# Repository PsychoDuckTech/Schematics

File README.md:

# Schematic and PCB Files for PsychoDuck Tech PCBs

## Notes
35? GPIO pins on the ESP32-S3

22 pins for the keyboard - 6 rows, 16 cols

with the multiplexer - 11 pins - 6 rows, 5 cols

## Tutorial Brovsky
`git add -A`

`git commit -m "message here"`

`git push`

[Extensive Tutorial...](https://github.com/PsychoDuckTech/Schematics/blob/main/GitExtensiveTutorial.md)

## Useful Resources
[KiCanvas](https://kicanvas.org/)

[Discord Server](https://discord.gg/zeTJYsWzsf)

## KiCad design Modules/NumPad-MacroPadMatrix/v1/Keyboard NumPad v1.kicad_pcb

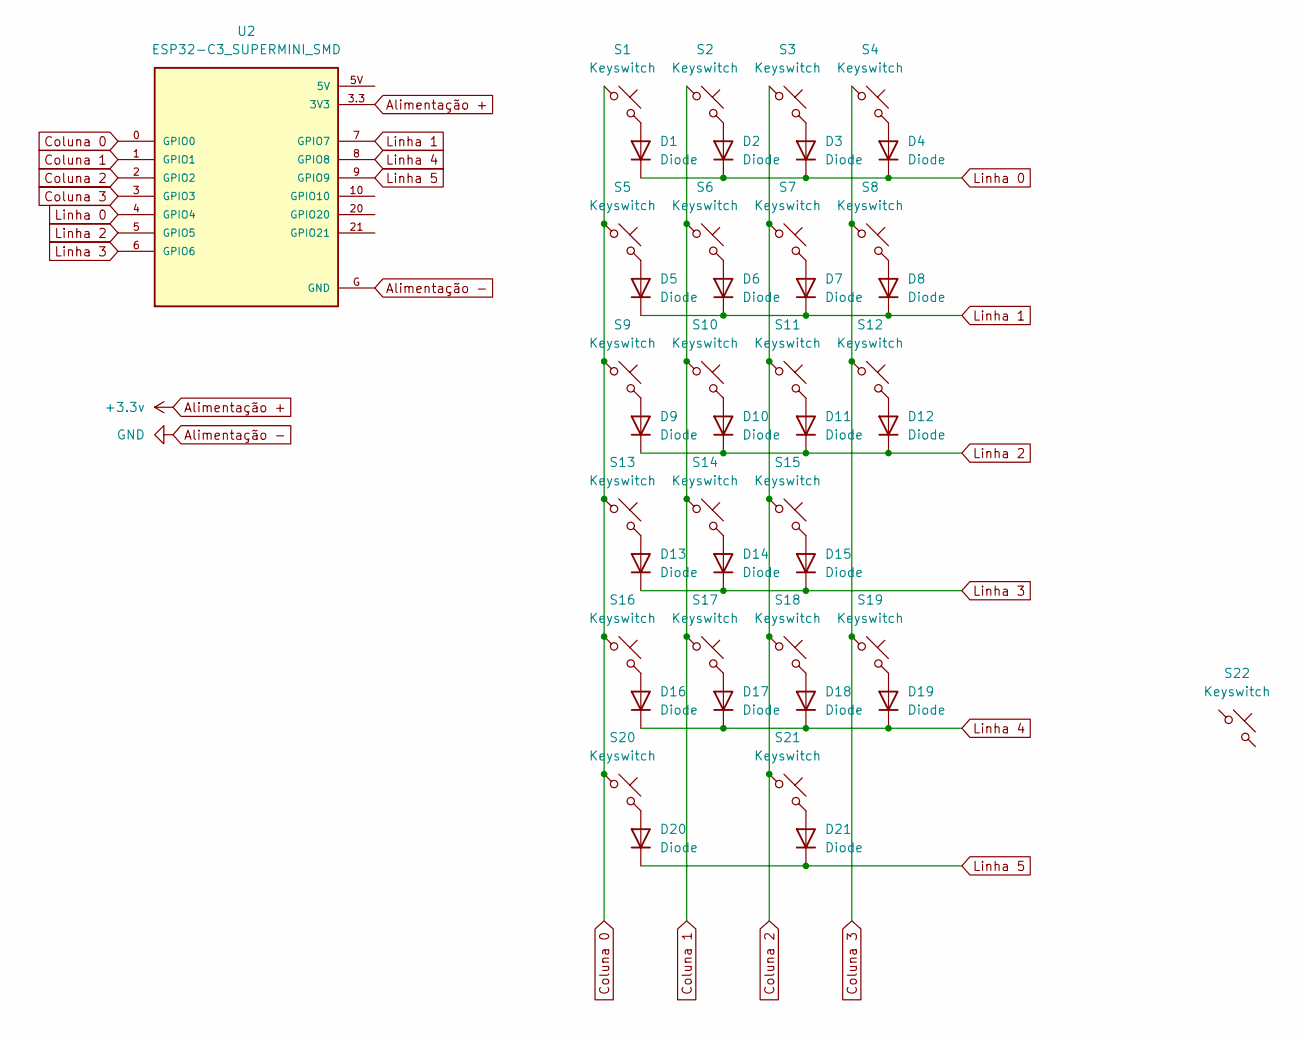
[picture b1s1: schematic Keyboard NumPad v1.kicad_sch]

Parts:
D1, D2, D3, D4, D5, D6, D7, D8, D9, D10, D11, D12, D13, D14, D15, D16, D17, D18, D19, D20, D21: Diode; D_DO-35_SOD27_P7.62mm_Horizontal
S1, S2, S3, S4, S5, S6, S7, S8, S9, S10, S11, S12, S13, S14, S15, S16, S17, S18, S19, S20, S21: Keyswitch; Hotswap_MX_Plated_1.00u
S22: Keyswitch; Cherry-MX-Low-Profile
U2: ESP32-C3_SUPERMINI_SMD; ESP32-C3_SUPERMINI

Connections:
Alimentação +: U2.3.3 (3V3)
Alimentação -: U2.G (GND)
Coluna 0: S1.1, S5.1, S9.1, S13.1, S16.1, S20.1, U2.0 (GPIO0)
Coluna 1: S2.1, S6.1, S10.1, S14.1, S17.1, U2.1 (GPIO1)
Coluna 2: S3.1, S7.1, S11.1, S15.1, S18.1, S21.1, U2.2 (GPIO2)
Coluna 3: S4.1, S8.1, S12.1, S19.1, U2.3 (GPIO3)
Linha 0: D1.1 (K), D2.1 (K), D3.1 (K), D4.1 (K), U2.4 (GPIO4)
Linha 1: D5.1 (K), D6.1 (K), D7.1 (K), D8.1 (K), U2.7 (GPIO7)
Linha 2: D9.1 (K), D10.1 (K), D11.1 (K), D12.1 (K), U2.5 (GPIO5)
Linha 3: D13.1 (K), D14.1 (K), D15.1 (K), U2.6 (GPIO6)
Linha 4: D16.1 (K), D17.1 (K), D18.1 (K), D19.1 (K), U2.8 (GPIO8)
Linha 5: D20.1 (K), D21.1 (K), U2.9 (GPIO9)
unnamed: D1.2 (A), S1.2
unnamed: D2.2 (A), S2.2
unnamed: D3.2 (A), S3.2
unnamed: D4.2 (A), S4.2
unnamed: D5.2 (A), S5.2
unnamed: D6.2 (A), S6.2
unnamed: D7.2 (A), S7.2
unnamed: D8.2 (A), S8.2
unnamed: D9.2 (A), S9.2
unnamed: D10.2 (A), S10.2
unnamed: D11.2 (A), S11.2
unnamed: D12.2 (A), S12.2
unnamed: D13.2 (A), S13.2
unnamed: D14.2 (A), S14.2
unnamed: D15.2 (A), S15.2
unnamed: D16.2 (A), S16.2
unnamed: D17.2 (A), S17.2
unnamed: D18.2 (A), S18.2
unnamed: D19.2 (A), S19.2
unnamed: D20.2 (A), S20.2
unnamed: D21.2 (A), S21.2

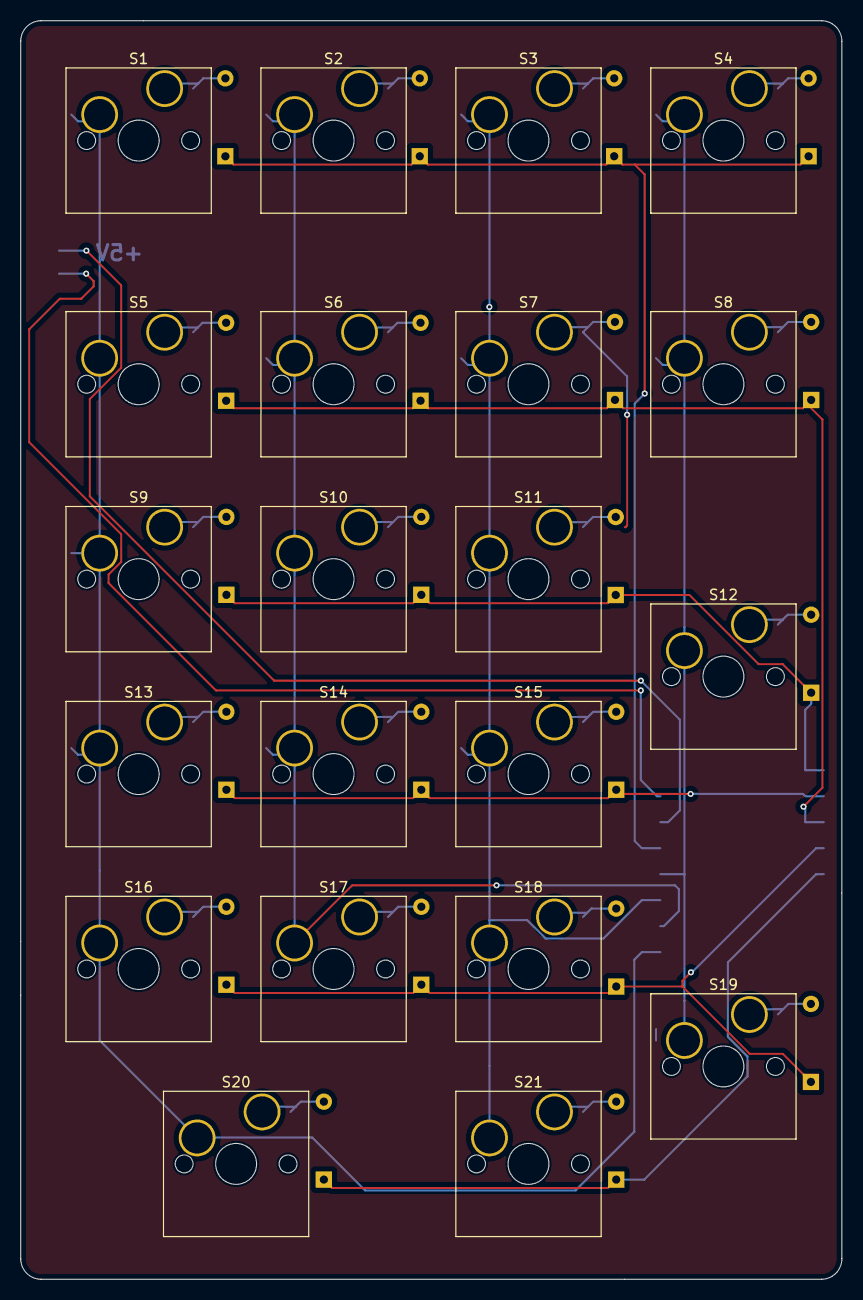
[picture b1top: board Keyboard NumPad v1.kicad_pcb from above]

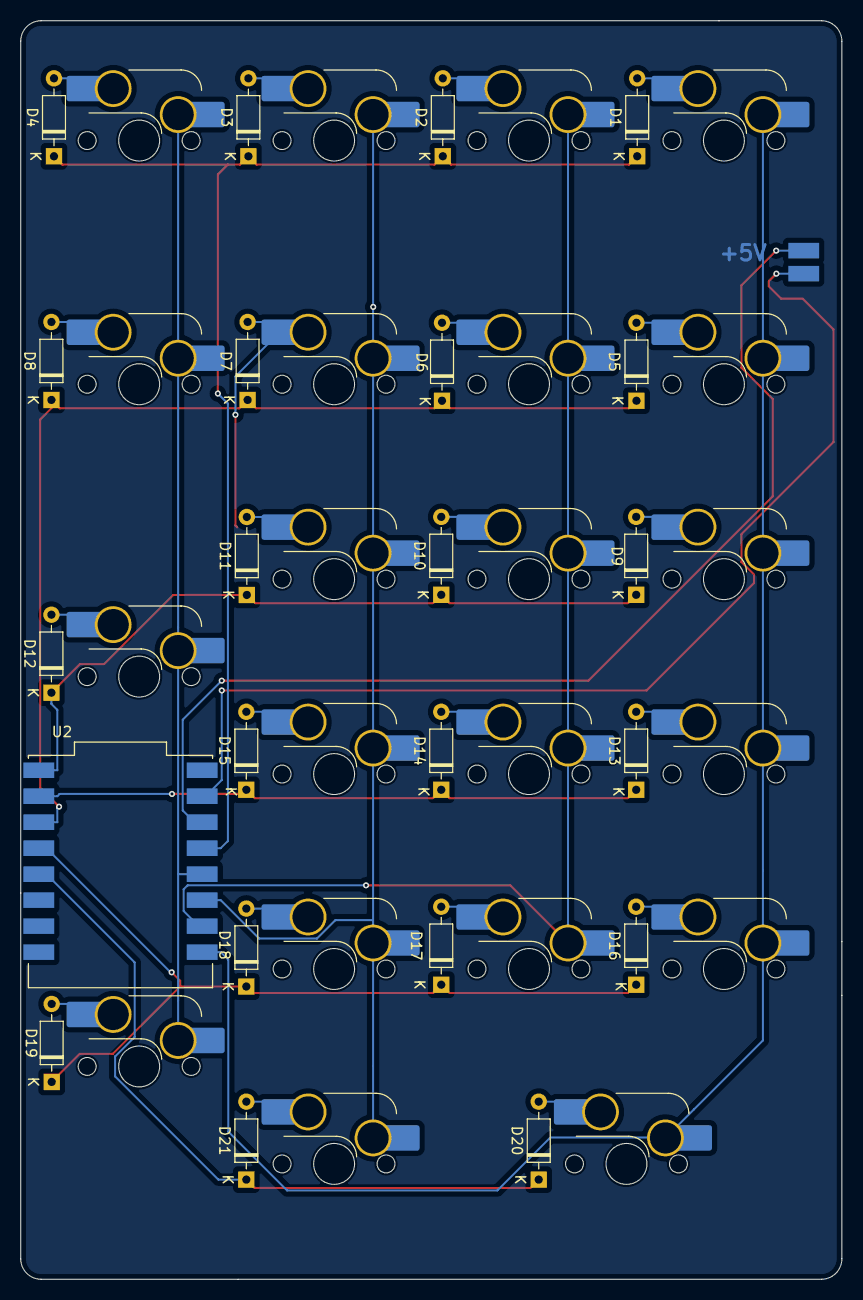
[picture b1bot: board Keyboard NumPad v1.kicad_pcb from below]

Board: 2 copper layers, 80.2 x 123.0 mm, 43 parts (22 on the bottom side), 31 nets.

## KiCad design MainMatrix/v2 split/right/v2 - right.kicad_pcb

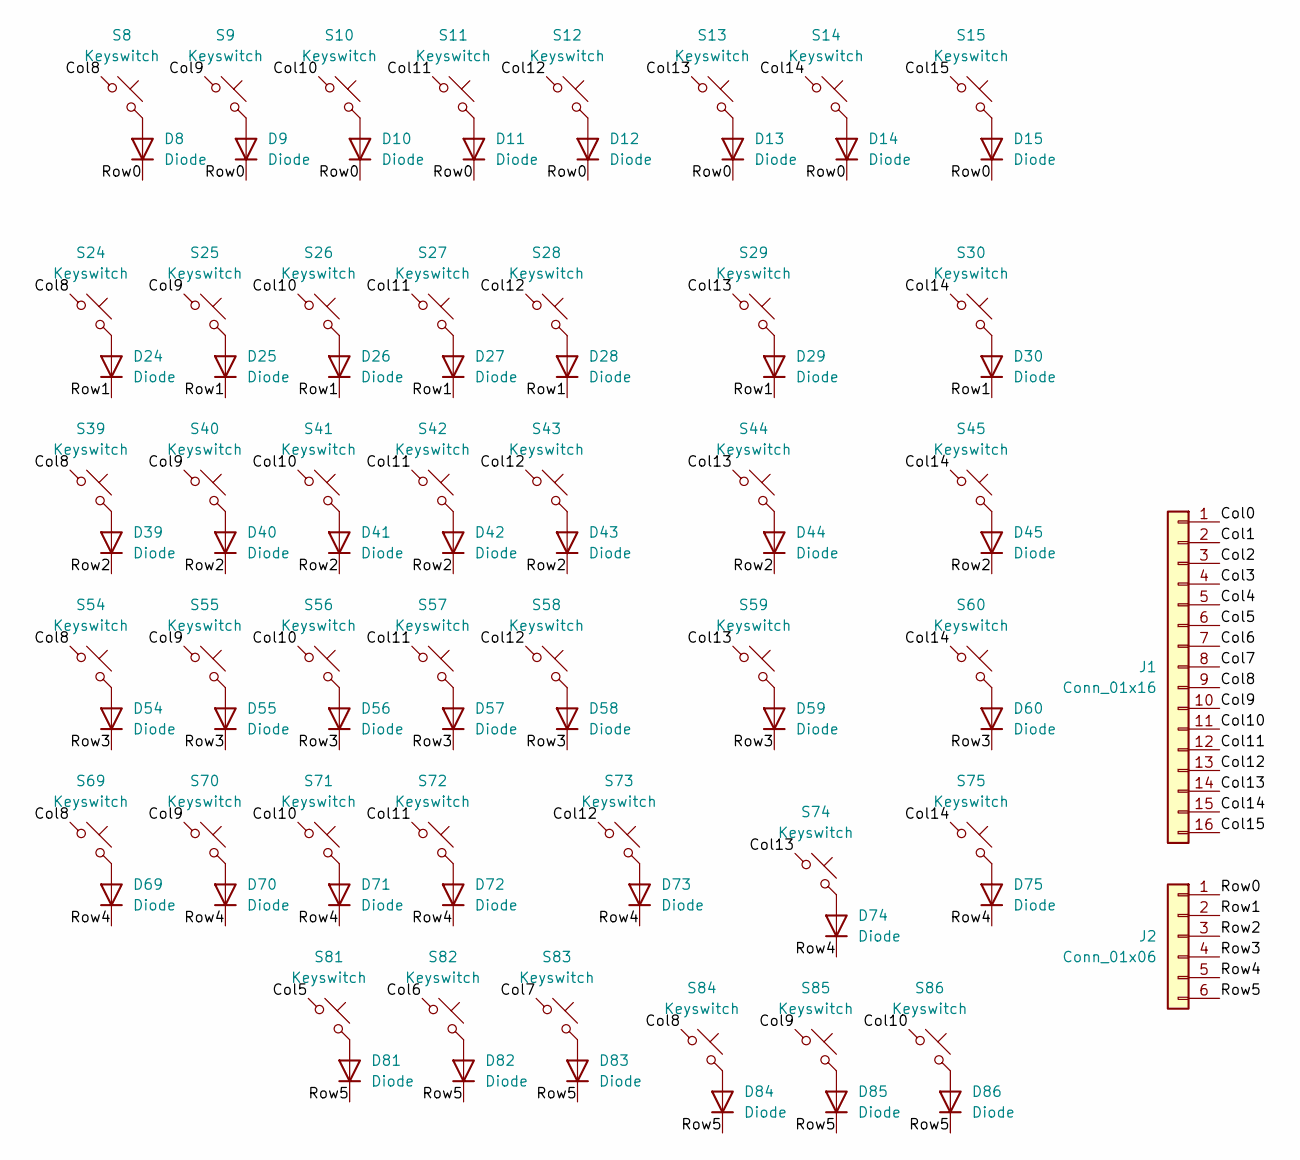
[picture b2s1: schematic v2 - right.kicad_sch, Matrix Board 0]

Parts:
D8, D9, D10, D11, D12, D13, D14, D15, D24, D25, D26, D27, D28, D29, D30, D39, D40, D41, D42, D43, D44, D45, D54, D55, D56, D57, D58, D59, D60, D69, D70, D71, D72, D73, D74, D75, D81, D82, D83, D84, D85, D86: Diode; D_DO-35_SOD27_P10.16mm_Horizontal
J1: Conn_01x16; PinSocket_1x16_P2.54mm_Vertical
J2: Conn_01x06; PinHeader_1x06_P2.54mm_Vertical
S8, S9, S10, S11, S12, S13, S14, S15, S24, S25, S26, S27, S28, S29, S30, S39, S40, S41, S42, S43, S44, S45, S54, S55, S56, S57, S58, S59, S60, S69, S70, S71, S72, S73, S74, S75, S81, S82, S83, S84, S85, S86: Keyswitch; Hotswap_MX_1.00u

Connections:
/Col0: J1.1
/Col1: J1.2
/Col2: J1.3
/Col3: J1.4
/Col4: J1.5
/Col5: J1.6, S81.1
/Col6: J1.7, S82.1
/Col7: J1.8, S83.1
/Col8: J1.9, S8.1, S24.1, S39.1, S54.1, S69.1, S84.1
/Col9: J1.10, S9.1, S25.1, S40.1, S55.1, S70.1, S85.1
/Col10: J1.11, S10.1, S26.1, S41.1, S56.1, S71.1, S86.1
/Col11: J1.12, S11.1, S27.1, S42.1, S57.1, S72.1
/Col12: J1.13, S12.1, S28.1, S43.1, S58.1, S73.1
/Col13: J1.14, S13.1, S29.1, S44.1, S59.1, S74.1
/Col14: J1.15, S14.1, S30.1, S45.1, S60.1, S75.1
/Col15: J1.16, S15.1
/Row0: D8.1 (K), D9.1 (K), D10.1 (K), D11.1 (K), D12.1 (K), D13.1 (K), D14.1 (K), D15.1 (K), J2.1
/Row1: D24.1 (K), D25.1 (K), D26.1 (K), D27.1 (K), D28.1 (K), D29.1 (K), D30.1 (K), J2.2
/Row2: D39.1 (K), D40.1 (K), D41.1 (K), D42.1 (K), D43.1 (K), D44.1 (K), D45.1 (K), J2.3
/Row3: D54.1 (K), D55.1 (K), D56.1 (K), D57.1 (K), D58.1 (K), D59.1 (K), D60.1 (K), J2.4
/Row4: D69.1 (K), D70.1 (K), D71.1 (K), D72.1 (K), D73.1 (K), D74.1 (K), D75.1 (K), J2.5
/Row5: D81.1 (K), D82.1 (K), D83.1 (K), D84.1 (K), D85.1 (K), D86.1 (K), J2.6
unnamed: D8.2 (A), S8.2
unnamed: D9.2 (A), S9.2
unnamed: D10.2 (A), S10.2
unnamed: D11.2 (A), S11.2
unnamed: D12.2 (A), S12.2
unnamed: D13.2 (A), S13.2
unnamed: D14.2 (A), S14.2
unnamed: D15.2 (A), S15.2
unnamed: D24.2 (A), S24.2
unnamed: D25.2 (A), S25.2
unnamed: D26.2 (A), S26.2
unnamed: D27.2 (A), S27.2
unnamed: D28.2 (A), S28.2
unnamed: D29.2 (A), S29.2
unnamed: D30.2 (A), S30.2
unnamed: D39.2 (A), S39.2
unnamed: D40.2 (A), S40.2
unnamed: D41.2 (A), S41.2
unnamed: D42.2 (A), S42.2
unnamed: D43.2 (A), S43.2
unnamed: D44.2 (A), S44.2
unnamed: D45.2 (A), S45.2
unnamed: D54.2 (A), S54.2
unnamed: D55.2 (A), S55.2
unnamed: D56.2 (A), S56.2
unnamed: D57.2 (A), S57.2
unnamed: D58.2 (A), S58.2
unnamed: D59.2 (A), S59.2
unnamed: D60.2 (A), S60.2
unnamed: D69.2 (A), S69.2
unnamed: D70.2 (A), S70.2
unnamed: D71.2 (A), S71.2
unnamed: D72.2 (A), S72.2
unnamed: D73.2 (A), S73.2
unnamed: D74.2 (A), S74.2
unnamed: D75.2 (A), S75.2
unnamed: D81.2 (A), S81.2
unnamed: D82.2 (A), S82.2
unnamed: D83.2 (A), S83.2
unnamed: D84.2 (A), S84.2
unnamed: D85.2 (A), S85.2
unnamed: D86.2 (A), S86.2

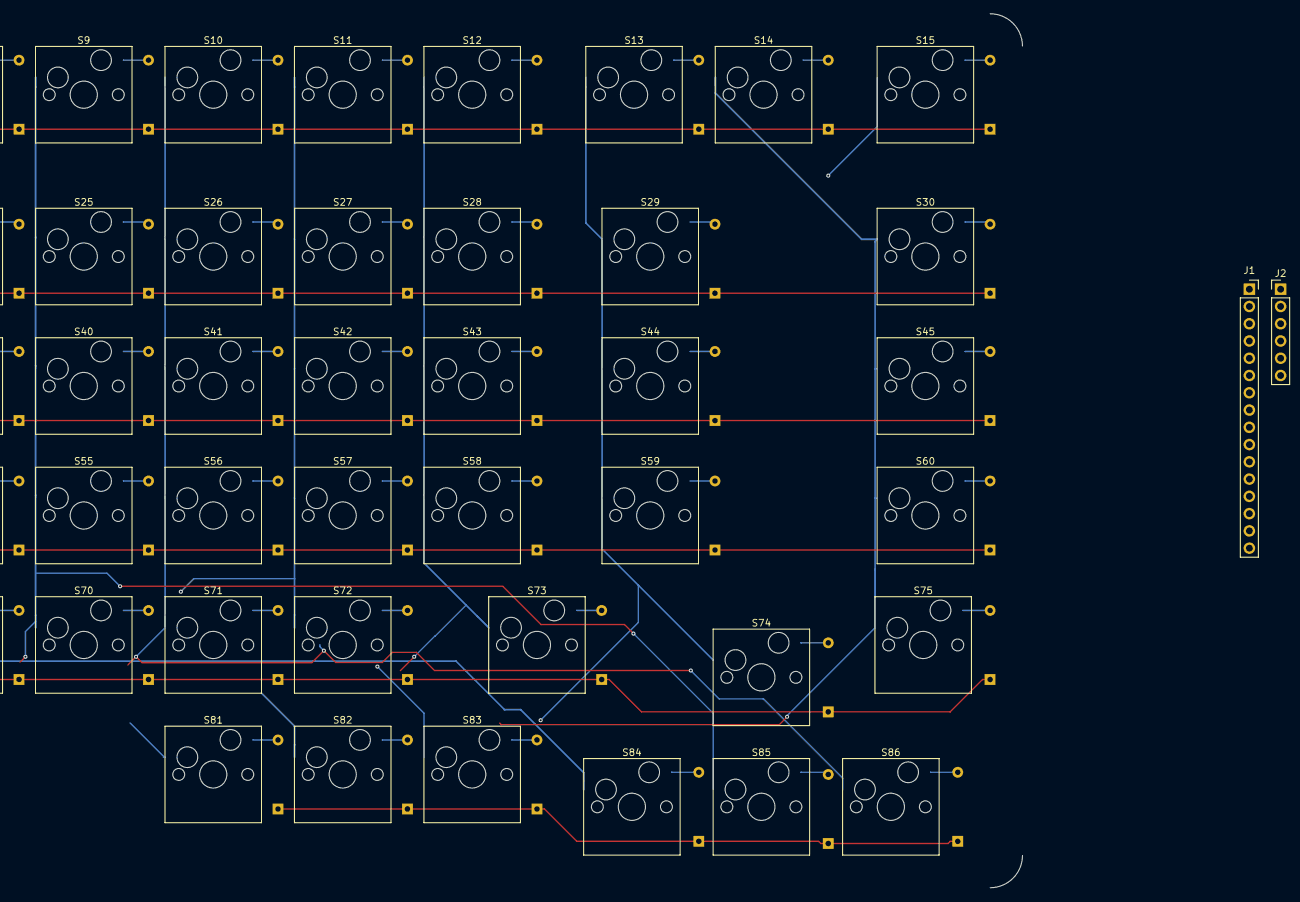
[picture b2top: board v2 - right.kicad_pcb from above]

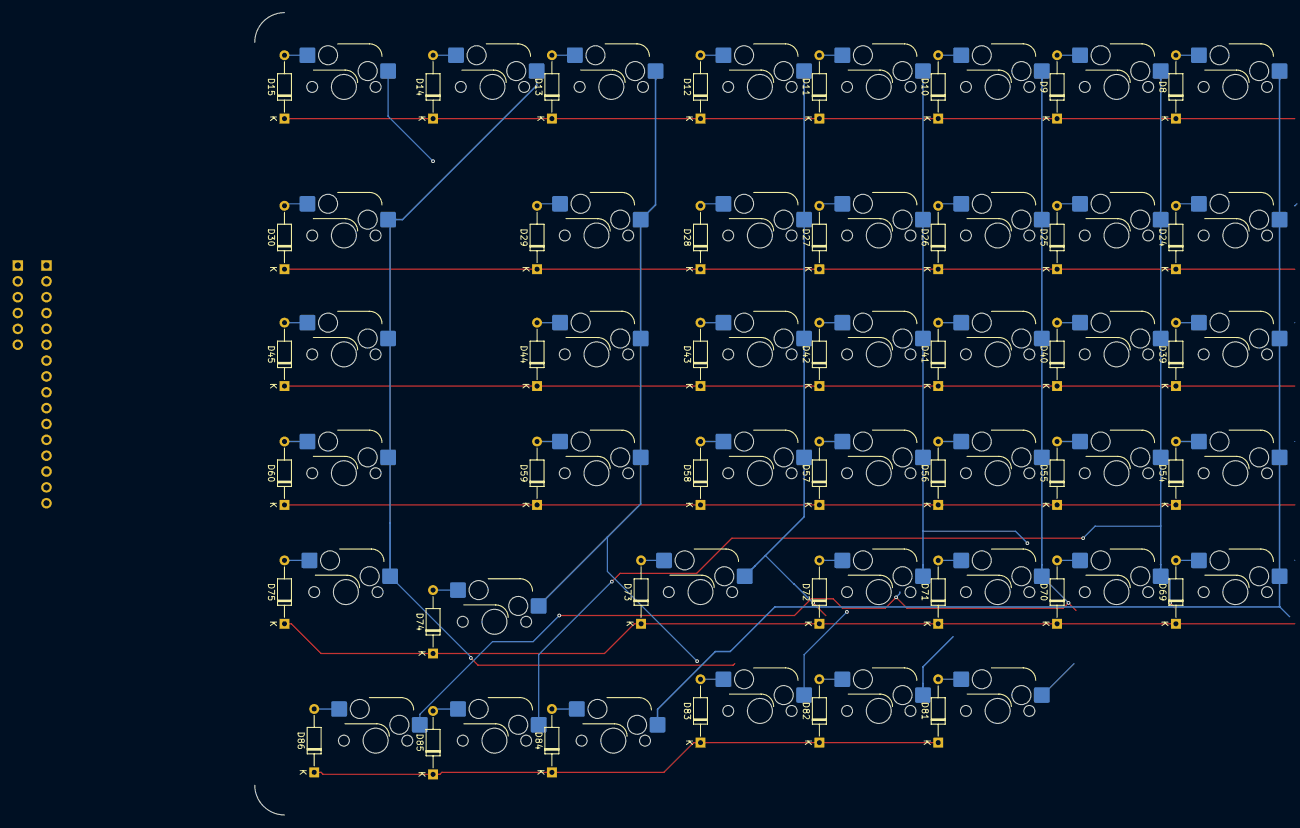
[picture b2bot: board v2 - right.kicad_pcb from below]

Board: 2 copper layers, 86 parts (42 on the bottom side), 59 nets.

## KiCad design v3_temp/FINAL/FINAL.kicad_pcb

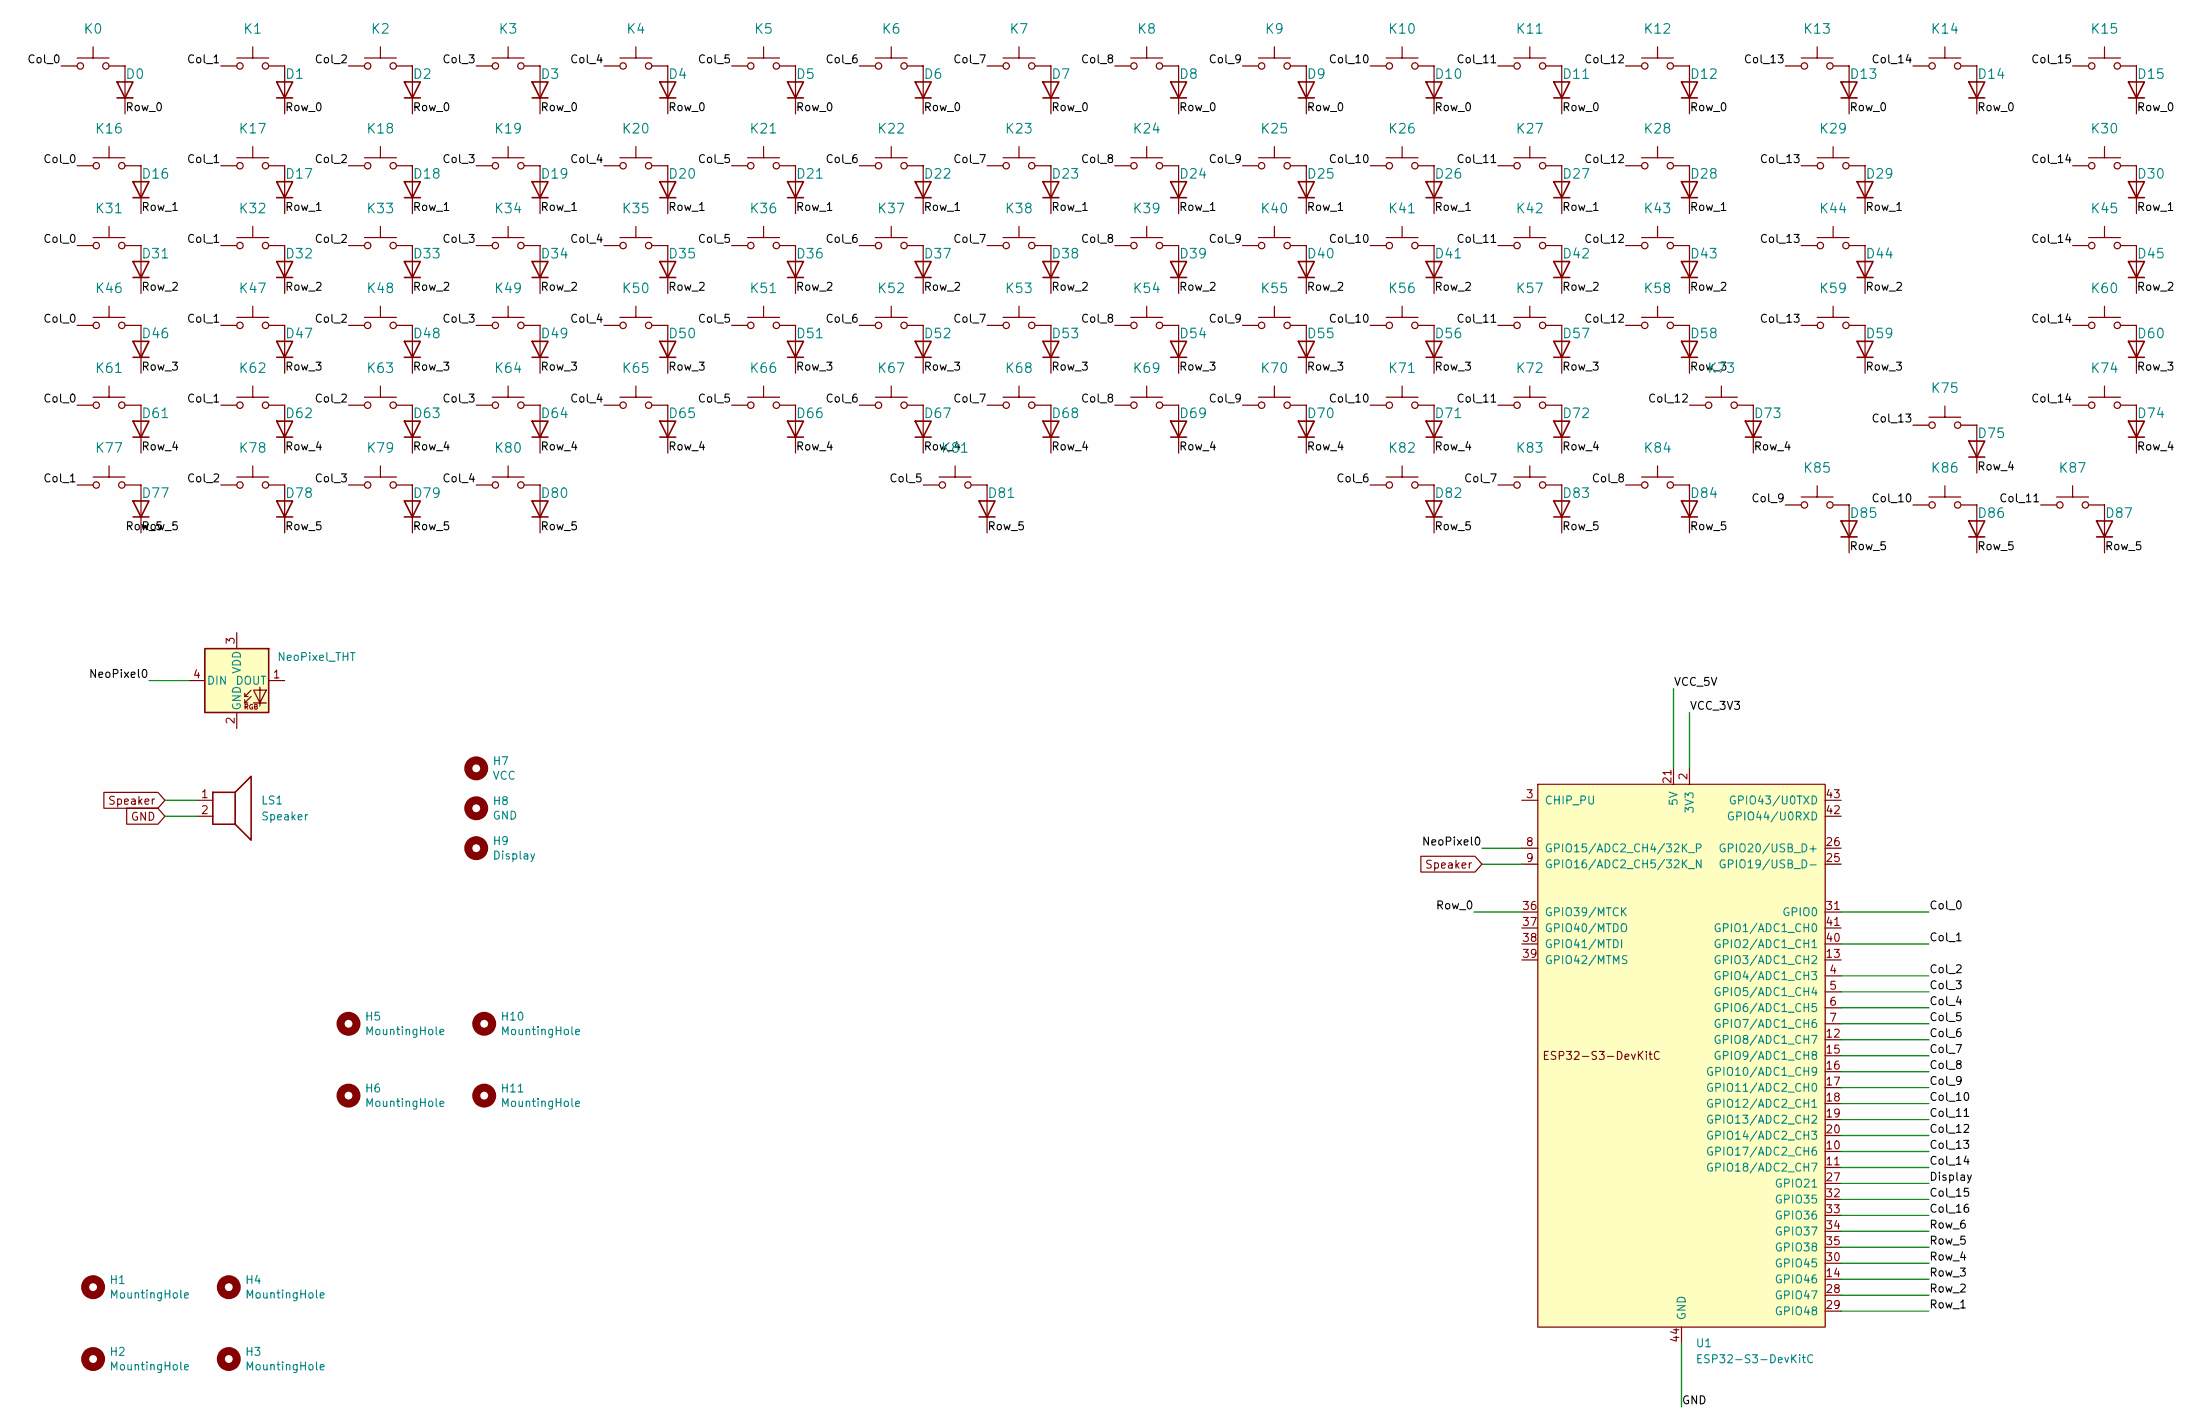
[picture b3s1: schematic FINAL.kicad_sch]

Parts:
D0, D1, D2, D3, D4, D5, D6, D7, D8, D9, D10, D11, D12, D13, D14, D15, D16, D17, D18, D19, D20, D21, D22, D23, D24, D25, D26, D27, D28, D29, D30, D31, D32, D33, D34, D35, D36, D37, D38, D39, D40, D41, D42, D43, D44, D45, D46, D47, D48, D49, D50, D51, D52, D53, D54, D55, D56, D57, D58, D59, D60, D61, D62, D63, D64, D65, D66, D67, D68, D69, D70, D71, D72, D73, D74, D75, D77, D78, D79, D80, D81, D82, D83, D84, D85, D86, D87: D; D_0805_2012Metric_Pad1.15x1.40mm_HandSolder
D88: NeoPixel_THT
H1, H2, H3, H4, H5, H6, H10, H11: MountingHole; MountingHole_3.2mm_M3_DIN965
H7: VCC; MountingHole_3.2mm_M3_DIN965
H8: GND; MountingHole_3.2mm_M3_DIN965
H9: Display; MountingHole_3.2mm_M3_DIN965
K0: ESC; SW_Cherry_MX_1.00u_PCB
K1: F1; SW_Cherry_MX_1.00u_PCB
K2: F2; SW_Cherry_MX_1.00u_PCB
K3: F3; SW_Cherry_MX_1.00u_PCB
K4: F4; SW_Cherry_MX_1.00u_PCB
K5: F5; SW_Cherry_MX_1.00u_PCB
K6: F6; SW_Cherry_MX_1.00u_PCB
K7: F7; SW_Cherry_MX_1.00u_PCB
K8: F8; SW_Cherry_MX_1.00u_PCB
K9: F9; SW_Cherry_MX_1.00u_PCB
K10: F10; SW_Cherry_MX_1.00u_PCB
K11: F11; SW_Cherry_MX_1.00u_PCB
K12: F12; SW_Cherry_MX_1.00u_PCB
K13: PRT; SW_Cherry_MX_1.00u_PCB
K14: INS; SW_Cherry_MX_1.00u_PCB
K15: DEL; SW_Cherry_MX_1.00u_PCB
K16: |,\; SW_Cherry_MX_1.25u_PCB
K17: !,,,,,,,,,1; SW_Cherry_MX_1.00u_PCB
K18: ",@,,,,,,,,2; SW_Cherry_MX_1.00u_PCB
K19: #,£,,,,,,,,3; SW_Cherry_MX_1.00u_PCB
K20: $,§,,,,,,,,4; SW_Cherry_MX_1.00u_PCB
K21: %,€,,,,,,,,5; SW_Cherry_MX_1.00u_PCB
K22: &,,,,,,,,,6; SW_Cherry_MX_1.00u_PCB
K23: /,{,,,,,,,,7; SW_Cherry_MX_1.00u_PCB
K24: (,[,,,,,,,,8; SW_Cherry_MX_1.00u_PCB
K25: ),],,,,,,,,9; SW_Cherry_MX_1.00u_PCB
K26: =,},,,,,,,,0; SW_Cherry_MX_1.00u_PCB
K27: ?,'; SW_Cherry_MX_1.00u_PCB
K28: »,«; SW_Cherry_MX_1.00u_PCB
K29: BACKSPACE; SW_Cherry_MX_1.75u_PCB
K30: HOME; SW_Cherry_MX_1.00u_PCB
K31: TAB; SW_Cherry_MX_1.25u_PCB
K32: Q; SW_Cherry_MX_1.00u_PCB
K33: W; SW_Cherry_MX_1.00u_PCB
K34: E; SW_Cherry_MX_1.00u_PCB
K35: R; SW_Cherry_MX_1.00u_PCB
K36: T; SW_Cherry_MX_1.00u_PCB
K37: Y; SW_Cherry_MX_1.00u_PCB
K38: U; SW_Cherry_MX_1.00u_PCB
K39: I; SW_Cherry_MX_1.00u_PCB
K40: O; SW_Cherry_MX_1.00u_PCB
K41: P; SW_Cherry_MX_1.00u_PCB
K42: *,+; SW_Cherry_MX_1.00u_PCB
K43: `,´; SW_Cherry_MX_1.00u_PCB
K44: Blank; SW_Cherry_MX_1.75u_PCB
K45: END; SW_Cherry_MX_1.00u_PCB
K46: CAPS; SW_Cherry_MX_1.25u_PCB
K47: A; SW_Cherry_MX_1.00u_PCB
K48: S; SW_Cherry_MX_1.00u_PCB
K49: D; SW_Cherry_MX_1.00u_PCB
K50: F; SW_Cherry_MX_1.00u_PCB
K51: G; SW_Cherry_MX_1.00u_PCB
K52: H; SW_Cherry_MX_1.00u_PCB
K53: J; SW_Cherry_MX_1.00u_PCB
K54: K; SW_Cherry_MX_1.00u_PCB
K55: L; SW_Cherry_MX_1.00u_PCB
K56: Ç; SW_Cherry_MX_1.00u_PCB
K57: ª,º; SW_Cherry_MX_1.00u_PCB
K58: ^,~~; SW_Cherry_MX_1.00u_PCB
K59: ENTER; SW_Cherry_MX_1.75u_PCB
K60: PGUP; SW_Cherry_MX_1.00u_PCB
K61: SHIFT; SW_Cherry_MX_1.25u_PCB
K62: >,,,,,,,,,<; SW_Cherry_MX_1.00u_PCB
K63: Z; SW_Cherry_MX_1.00u_PCB
K64: X; SW_Cherry_MX_1.00u_PCB
K65: C; SW_Cherry_MX_1.00u_PCB
K66: V; SW_Cherry_MX_1.00u_PCB
K67: B; SW_Cherry_MX_1.00u_PCB
K68: N; SW_Cherry_MX_1.00u_PCB
K69: M; SW_Cherry_MX_1.00u_PCB
K70: ;,,; SW_Cherry_MX_1.00u_PCB
K71: :,.; SW_Cherry_MX_1.00u_PCB
K72: -,_; SW_Cherry_MX_1.00u_PCB
K73: SHIFT; SW_Cherry_MX_2.00u_PCB
K74: PGDN; SW_Cherry_MX_1.00u_PCB
K75: ∧; SW_Cherry_MX_1.00u_PCB
K77: CTRL; SW_Cherry_MX_1.25u_PCB
K78: SUPER; SW_Cherry_MX_1.00u_PCB
K79, K83: <i class='fa fa-circle'></i>; SW_Cherry_MX_1.00u_PCB
K80, K82: ALT; SW_Cherry_MX_1.00u_PCB
K81: Blank; SW_Cherry_MX_2.75u_PCB
K84: CTRL; SW_Cherry_MX_1.00u_PCB
K85: <; SW_Cherry_MX_1.00u_PCB
K86: ∨; SW_Cherry_MX_1.00u_PCB
K87: >; SW_Cherry_MX_1.00u_PCB
LS1: Speaker
U1: ESP32-S3-DevKitC

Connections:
/Col_0: K0.1, K16.1, K31.1, K46.1, K61.1, U1.31 (GPIO0)
/Col_1: K1.1, K17.1, K32.1, K47.1, K62.1, K77.1, U1.40 (GPIO2/ADC1_CH1)
/Col_2: K2.1, K18.1, K33.1, K48.1, K63.1, K78.1, U1.4 (GPIO4/ADC1_CH3)
/Col_3: K3.1, K19.1, K34.1, K49.1, K64.1, K79.1, U1.5 (GPIO5/ADC1_CH4)
/Col_4: K4.1, K20.1, K35.1, K50.1, K65.1, K80.1, U1.6 (GPIO6/ADC1_CH5)
/Col_5: K5.1, K21.1, K36.1, K51.1, K66.1, K81.1, U1.7 (GPIO7/ADC1_CH6)
/Col_6: K6.1, K22.1, K37.1, K52.1, K67.1, K82.1, U1.12 (GPIO8/ADC1_CH7)
/Col_7: K7.1, K23.1, K38.1, K53.1, K68.1, K83.1, U1.15 (GPIO9/ADC1_CH8)
/Col_8: K8.1, K24.1, K39.1, K54.1, K69.1, K84.1, U1.16 (GPIO10/ADC1_CH9)
/Col_9: K9.1, K25.1, K40.1, K55.1, K70.1, K85.1, U1.17 (GPIO11/ADC2_CH0)
/Col_10: K10.1, K26.1, K41.1, K56.1, K71.1, K86.1, U1.18 (GPIO12/ADC2_CH1)
/Col_11: K11.1, K27.1, K42.1, K57.1, K72.1, K87.1, U1.19 (GPIO13/ADC2_CH2)
/Col_12: K12.1, K28.1, K43.1, K58.1, K73.1, U1.20 (GPIO14/ADC2_CH3)
/Col_13: K13.1, K29.1, K44.1, K59.1, K75.1, U1.10 (GPIO17/ADC2_CH6)
/Col_14: K14.1, K30.1, K45.1, K60.1, K74.1, U1.11 (GPIO18/ADC2_CH7)
/Col_15: K15.1, U1.32 (GPIO35)
/Col_16: U1.33 (GPIO36)
/Display: U1.27 (GPIO21)
/NeoPixel0: D88.4 (DIN), U1.8 (GPIO15/ADC2_CH4/32K_P)
/Row_0: D0.1 (K), D1.1 (K), D2.1 (K), D3.1 (K), D4.1 (K), D5.1 (K), D6.1 (K), D7.1 (K), D8.1 (K), D9.1 (K), D10.1 (K), D11.1 (K), D12.1 (K), D13.1 (K), D14.1 (K), D15.1 (K), U1.36 (GPIO39/MTCK)
/Row_1: D16.1 (K), D17.1 (K), D18.1 (K), D19.1 (K), D20.1 (K), D21.1 (K), D22.1 (K), D23.1 (K), D24.1 (K), D25.1 (K), D26.1 (K), D27.1 (K), D28.1 (K), D29.1 (K), D30.1 (K), U1.29 (GPIO48)
/Row_2: D31.1 (K), D32.1 (K), D33.1 (K), D34.1 (K), D35.1 (K), D36.1 (K), D37.1 (K), D38.1 (K), D39.1 (K), D40.1 (K), D41.1 (K), D42.1 (K), D43.1 (K), D44.1 (K), D45.1 (K), U1.28 (GPIO47)
/Row_3: D46.1 (K), D47.1 (K), D48.1 (K), D49.1 (K), D50.1 (K), D51.1 (K), D52.1 (K), D53.1 (K), D54.1 (K), D55.1 (K), D56.1 (K), D57.1 (K), D58.1 (K), D59.1 (K), D60.1 (K), U1.14 (GPIO46)
/Row_4: D61.1 (K), D62.1 (K), D63.1 (K), D64.1 (K), D65.1 (K), D66.1 (K), D67.1 (K), D68.1 (K), D69.1 (K), D70.1 (K), D71.1 (K), D72.1 (K), D73.1 (K), D74.1 (K), D75.1 (K), U1.30 (GPIO45)
/Row_5: D77.1 (K), D78.1 (K), D79.1 (K), D80.1 (K), D81.1 (K), D82.1 (K), D83.1 (K), D84.1 (K), D85.1 (K), D86.1 (K), D87.1 (K), U1.35 (GPIO38)
/Row_6: U1.34 (GPIO37)
/VCC_3V3: U1.1 (3V3), U1.2 (3V3)
/VCC_5V: U1.21 (5V)
GND: U1.22 (GND), U1.23 (GND), U1.24 (GND), U1.44 (GND)
unnamed: D0.2 (A), K0.2
unnamed: D1.2 (A), K1.2
unnamed: D2.2 (A), K2.2
unnamed: D3.2 (A), K3.2
unnamed: D4.2 (A), K4.2
unnamed: D5.2 (A), K5.2
unnamed: D6.2 (A), K6.2
unnamed: D7.2 (A), K7.2
unnamed: D8.2 (A), K8.2
unnamed: D9.2 (A), K9.2
unnamed: D10.2 (A), K10.2
unnamed: D11.2 (A), K11.2
unnamed: D12.2 (A), K12.2
unnamed: D13.2 (A), K13.2
unnamed: D14.2 (A), K14.2
unnamed: D15.2 (A), K15.2
unnamed: D16.2 (A), K16.2
unnamed: D17.2 (A), K17.2
unnamed: D18.2 (A), K18.2
unnamed: D19.2 (A), K19.2
unnamed: D20.2 (A), K20.2
unnamed: D21.2 (A), K21.2
unnamed: D22.2 (A), K22.2
unnamed: D23.2 (A), K23.2
unnamed: D24.2 (A), K24.2
unnamed: D25.2 (A), K25.2
unnamed: D26.2 (A), K26.2
unnamed: D27.2 (A), K27.2
unnamed: D28.2 (A), K28.2
unnamed: D29.2 (A), K29.2
unnamed: D30.2 (A), K30.2
unnamed: D31.2 (A), K31.2
unnamed: D32.2 (A), K32.2
unnamed: D33.2 (A), K33.2
unnamed: D34.2 (A), K34.2
unnamed: D35.2 (A), K35.2
unnamed: D36.2 (A), K36.2
unnamed: D37.2 (A), K37.2
unnamed: D38.2 (A), K38.2
unnamed: D39.2 (A), K39.2
unnamed: D40.2 (A), K40.2
unnamed: D41.2 (A), K41.2
unnamed: D42.2 (A), K42.2
unnamed: D43.2 (A), K43.2
unnamed: D44.2 (A), K44.2
unnamed: D45.2 (A), K45.2
unnamed: D46.2 (A), K46.2
unnamed: D47.2 (A), K47.2
unnamed: D48.2 (A), K48.2
unnamed: D49.2 (A), K49.2
unnamed: D50.2 (A), K50.2
unnamed: D51.2 (A), K51.2
unnamed: D52.2 (A), K52.2
unnamed: D53.2 (A), K53.2
unnamed: D54.2 (A), K54.2
unnamed: D55.2 (A), K55.2
unnamed: D56.2 (A), K56.2
unnamed: D57.2 (A), K57.2
unnamed: D58.2 (A), K58.2
unnamed: D59.2 (A), K59.2
unnamed: D60.2 (A), K60.2
unnamed: D61.2 (A), K61.2
unnamed: D62.2 (A), K62.2
unnamed: D63.2 (A), K63.2
unnamed: D64.2 (A), K64.2
unnamed: D65.2 (A), K65.2
unnamed: D66.2 (A), K66.2
unnamed: D67.2 (A), K67.2
unnamed: D68.2 (A), K68.2
unnamed: D69.2 (A), K69.2
unnamed: D70.2 (A), K70.2
unnamed: D71.2 (A), K71.2
unnamed: D72.2 (A), K72.2
unnamed: D73.2 (A), K73.2
unnamed: D74.2 (A), K74.2
unnamed: D75.2 (A), K75.2
unnamed: D77.2 (A), K77.2
unnamed: D78.2 (A), K78.2
unnamed: D79.2 (A), K79.2
unnamed: D80.2 (A), K80.2
unnamed: D81.2 (A), K81.2
unnamed: D82.2 (A), K82.2
unnamed: D83.2 (A), K83.2
unnamed: D84.2 (A), K84.2
unnamed: D85.2 (A), K85.2
unnamed: D86.2 (A), K86.2
unnamed: D87.2 (A), K87.2
Speaker: LS1.1, U1.9 (GPIO16/ADC2_CH5/32K_N)

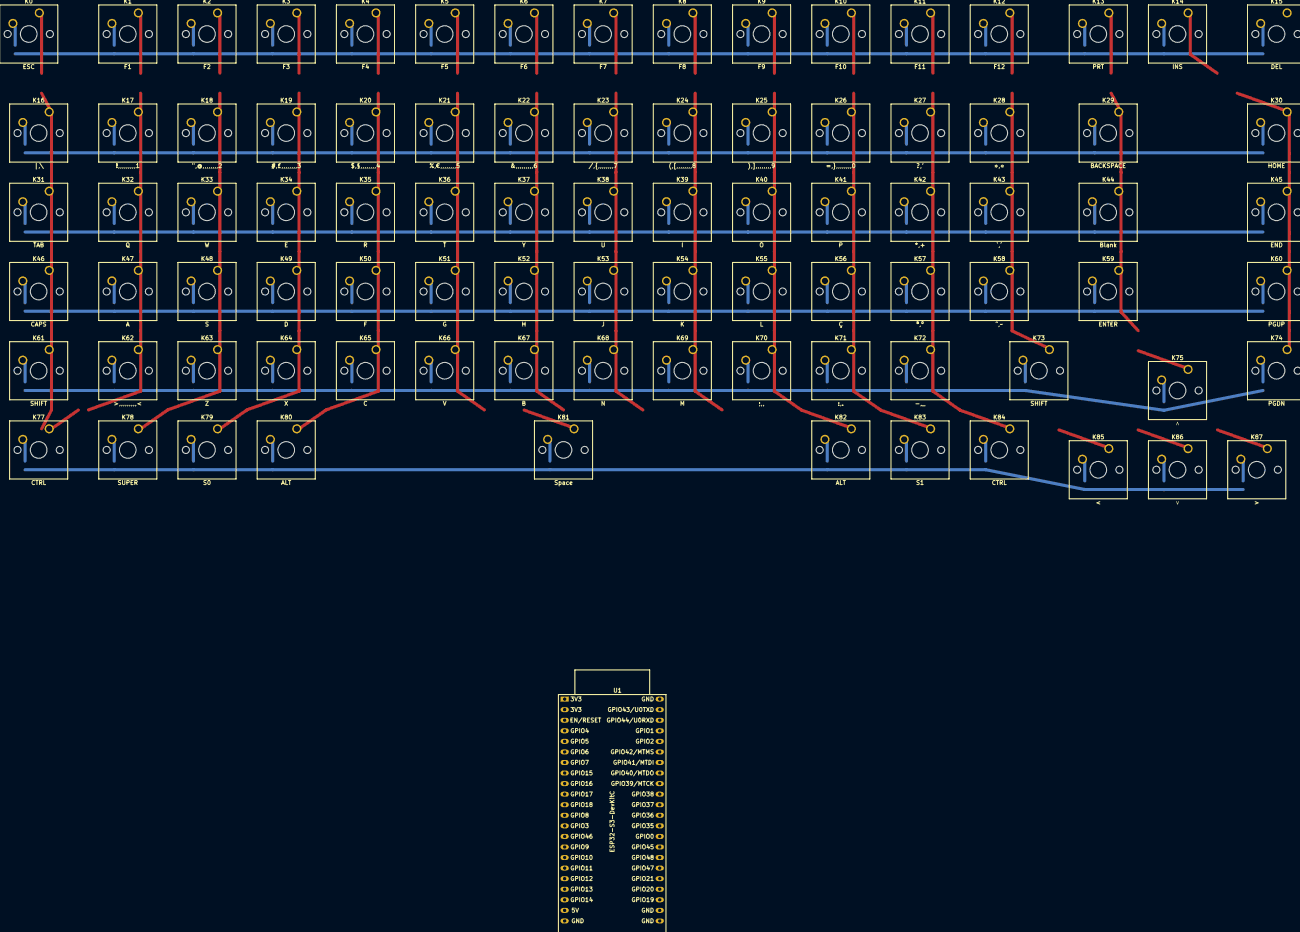
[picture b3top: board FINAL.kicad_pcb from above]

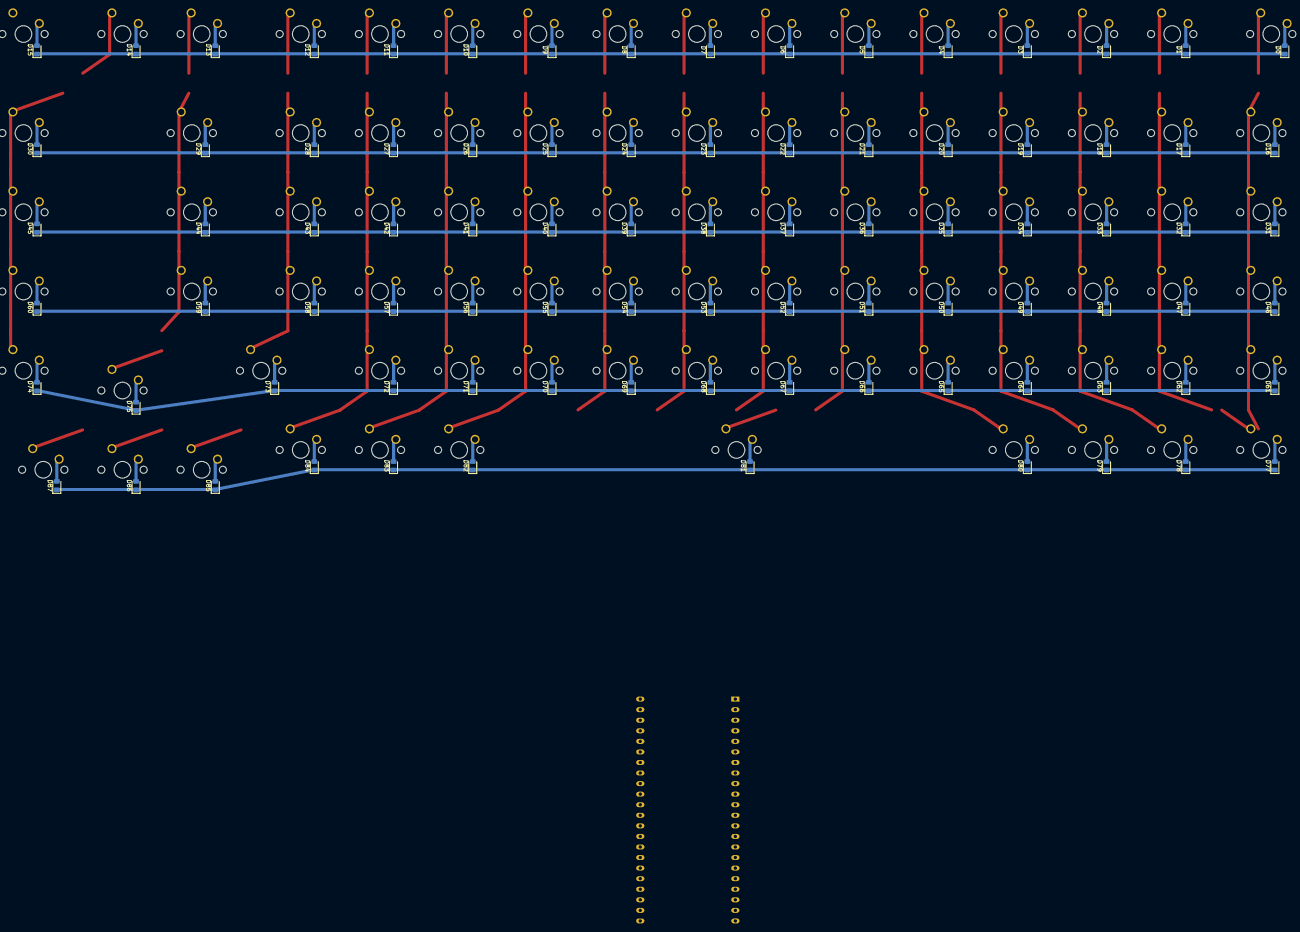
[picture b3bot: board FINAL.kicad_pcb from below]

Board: 2 copper layers, 182 parts (87 on the bottom side), 111 nets.

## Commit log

2024-09-16 Added a few files.
2024-09-16 Readjusted some folders and files.
2024-09-16 ignore
2024-09-16 Started Porting Schematics into v1 from v0
2024-09-16 Some file organization.
2024-09-16 Add files via upload
    Oops
2024-09-18 Create notes
2024-09-21 New Schematic files (v2_TEMP)
2024-09-21 idk whats happening
2024-10-02 added latest matrix schematic
2024-10-02 Recreated the Keyboard Matrix manually.
2024-10-02 clnup
2024-10-03 Updated the kicad schematics.
2024-10-03 remved the old v1 folder, as it had no working files
2024-10-03 this shit is hard to understand
2024-10-03 additions to the v1 pcb and schematics
2024-10-04 Finalised the Matrix PCB.
2024-10-04 Added some more copper. It's better this way.
2024-10-05 Cleaned up the v1 folder and fixed the previous commit.
2024-10-06 added module folder.
2024-10-07 Added the layout files from the online keyboard layout editor.
2024-10-07 Update README.md
    ADDED GIT COMMANDS
2024-10-09 Reorganized the repository. Added PD logo.
2024-10-09 Fixed v0.
2024-10-10 nothin
2024-10-10 Added more ducks :3
2024-10-10 More organization :P
2024-10-10 Regorganization. Again :)
2024-10-10 My unfinished Board :3
2024-10-10 Tidying up brovsky. UwU
2024-10-10 Some Repairs :3
2024-10-10 finishing the repairs :P
2024-10-10 Module Atualization :3
2024-10-10 V1 Version of the module :P
2024-10-11 Adjusted the Main Matrix. Adjusted the PCB logo.
2024-10-11 Created Main Matrix v2 split.
2024-10-11 Update README.md
    removed extensive tutorial. begining of port.
2024-10-11 Rename Git Extensive Tutorial.md to GitExtensiveTutorial.md
2024-10-11 Added shortcut link to the new extensive tutorial file.
2024-10-11 Cleaning up README.md
2024-10-12 iniciated the ControlerBoard V0. I need the screen size!!
2024-10-14 Starting fixes to NumpadMatrix v1
2024-10-14 Finishing fixes to NumpadMatrix v1
2024-10-14 Tidying up... :3
2024-11-01 added image exports for the MainMatrix v1 and the Numpad Module v1
2024-12-02 Version 2 of Matrix Module x_x
2024-12-03 Update of Module V2 x_x
2024-12-05 fuck x_x
2024-12-05 Filled copper regions on the numpad module
2024-12-06 fuck (again) x_x
2024-12-06 ControlBoard V0 :P
2025-01-13 message here
2025-01-13 Version 2 of the MainMatrix
2025-01-14 Updating Logos
2025-01-16 resolvendo merda :-:
2025-01-16 little things
2025-01-16 little things again :-:
2025-01-21 atualization of board versions 2.1
2025-03-08 Improvements to the MainMatrix board~
